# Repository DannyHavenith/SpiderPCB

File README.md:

Hardware Design for the Spider Home Automation Hub
==================================================
These files contain the schema and PCB-design for spider. More details in the 
[spider firmware repository](https://github.com/DannyHavenith/spider).

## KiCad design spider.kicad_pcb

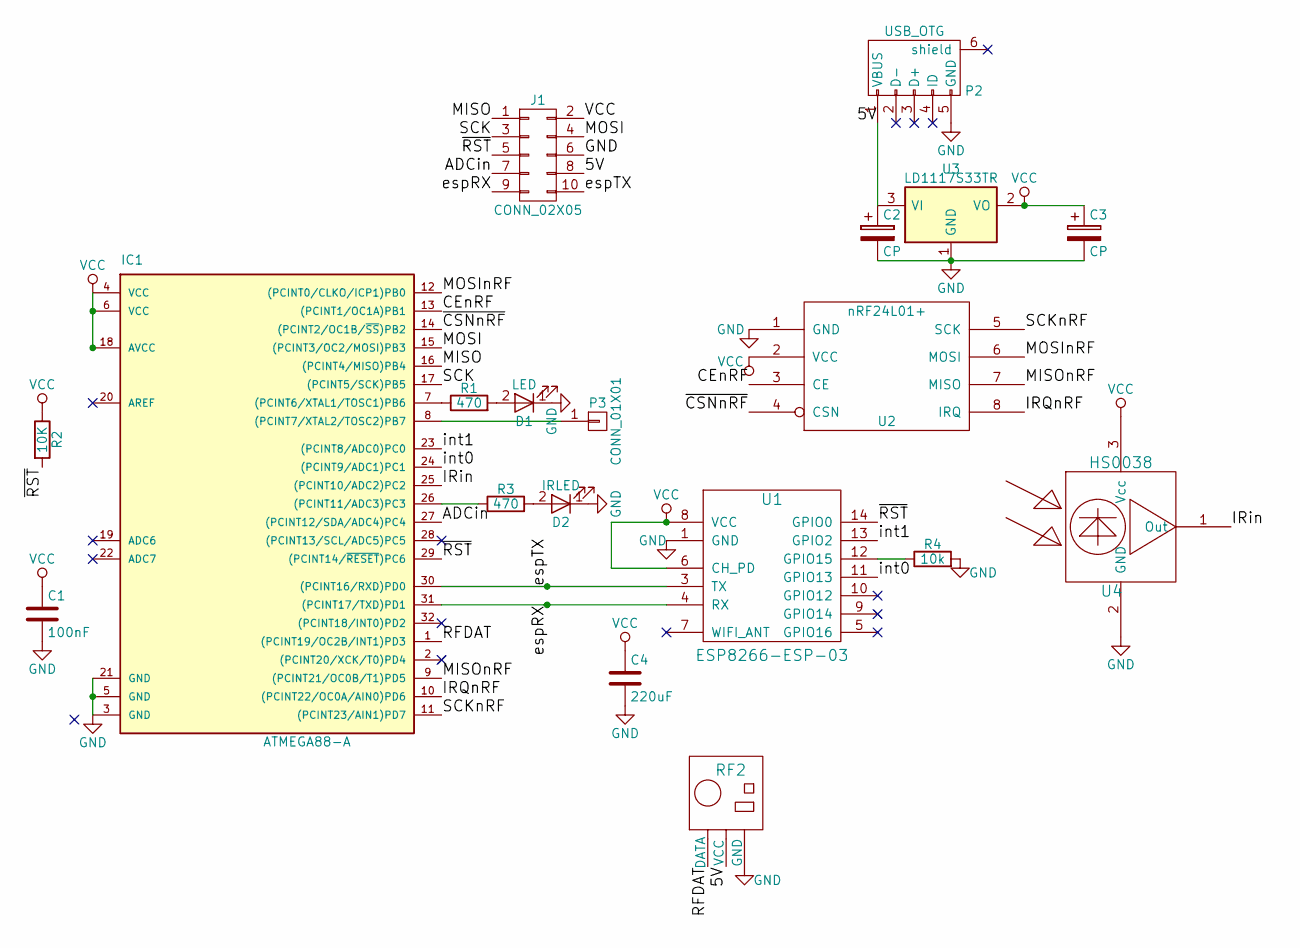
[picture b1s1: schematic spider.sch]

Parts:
C1: 100nF; C_0805
C2, C3: CP; CP_Elec_4x5.3
C4: 220uF; C_0805
D1: LED; LED_0805
D2: IRLED; LED_D5.0mm
IC1: ATMEGA88-A; TQFP-32_7x7mm_Pitch0.8mm
J1: CONN_02X05; Pin_Header_Straight_2x05_Pitch2.54mm
P2: USB_OTG; USB_Micro-B handsoldering
P3: CONN_01X01; Pin_Header_Straight_1x01_Pitch2.00mm
R1, R3: 470; R_0805_HandSoldering
R2: 10K; R_0805_HandSoldering
R4: 10k; R_0805_HandSoldering
RF2: 433 MHz; RF_Transmitter_433_MHz
U1: ESP8266-ESP-03
U2: nRF24L01+; NRF24L01_MODULE
U3: LD1117S33TR; SOT-223-3Lead_TabPin2
U4: HS0038; TSOP2438_long

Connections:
/5V: C2.1, J1.8, P2.1 (VBUS), RF2.2 (VCC), U3.3 (VI)
/ADCin: IC1.27 ((PCINT12/SDA/ADC4)PC4), J1.7
/CEnRF: IC1.13 ((PCINT1/OC1A)PB1), U2.3 (CE)
/IRQnRF: IC1.10 ((PCINT22/OC0A/AIN0)PD6), U2.8 (IRQ)
/IRin: IC1.25 ((PCINT10/ADC2)PC2), U4.1 (Out)
/MISO: IC1.16 ((PCINT4/MISO)PB4), J1.1
/MISOnRF: IC1.9 ((PCINT21/OC0B/T1)PD5), U2.7 (MISO)
/MOSI: IC1.15 ((PCINT3/OC2/MOSI)PB3), J1.4
/MOSInRF: IC1.12 ((PCINT0/CLKO/ICP1)PB0), U2.6 (MOSI)
/RFDAT: IC1.1 ((PCINT19/OC2B/INT1)PD3), RF2.1 (DATA)
/SCK: IC1.17 ((PCINT5/SCK)PB5), J1.3
/SCKnRF: IC1.11 ((PCINT23/AIN1)PD7), U2.5 (SCK)
/espRX: IC1.31 ((PCINT17/TXD)PD1), J1.9, U1.4 (RX)
/espTX: IC1.30 ((PCINT16/RXD)PD0), J1.10, U1.3 (TX)
/int0: IC1.24 ((PCINT9/ADC1)PC1), U1.11 (GPIO13)
/int1: IC1.23 ((PCINT8/ADC0)PC0), U1.13 (GPIO2)
/~CSNnRF: IC1.14 ((PCINT2/OC1B/~SS~)PB2), U2.4 (CSN)
/~RST: IC1.29 ((PCINT14/~RESET~)PC6), J1.5, R2.2, U1.14 (GPIO0)
GND: C1.2, C2.2, C3.2, C4.2, D1.1 (K), D2.1 (K), IC1.3 (GND), IC1.5 (GND), IC1.21 (GND), J1.6, P2.5 (GND), R4.2, RF2.3 (GND), U1.1 (GND), U2.1 (GND), U3.1 (GND), U4.2 (GND)
unnamed: D1.2 (A), R1.2
unnamed: D2.2 (A), R3.2
unnamed: IC1.7 ((PCINT6/XTAL1/TOSC1)PB6), R1.1
unnamed: IC1.8 ((PCINT7/XTAL2/TOSC2)PB7), P3.1
unnamed: IC1.26 ((PCINT11/ADC3)PC3), R3.1
unnamed: R4.1, U1.12 (GPIO15)
VCC: C1.1, C3.1, C4.1, IC1.4 (VCC), IC1.6 (VCC), IC1.18 (AVCC), J1.2, R2.1, U1.6 (CH_PD), U1.8 (VCC), U2.2 (VCC), U3.2 (VO), U4.3 (Vcc)

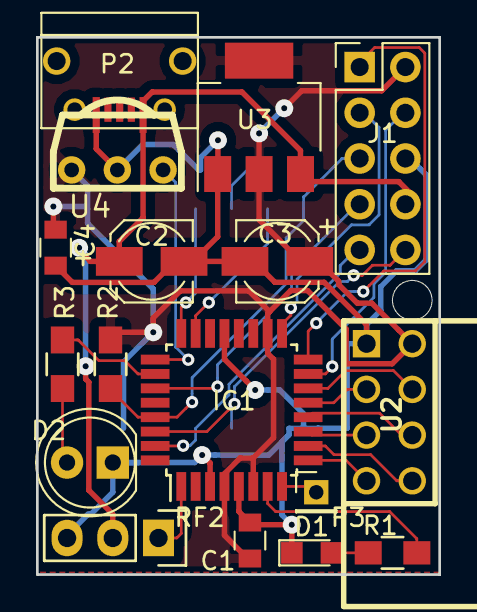
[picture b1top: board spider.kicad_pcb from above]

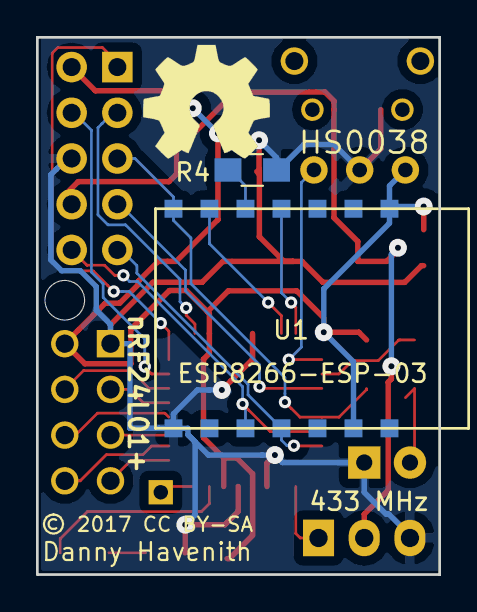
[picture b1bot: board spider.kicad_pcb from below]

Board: 2 copper layers, 22.4 x 29.8 mm, 20 parts (3 on the bottom side), 26 nets.

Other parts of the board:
© 2017 CC BY-SA: Danny Havenith; oshardware

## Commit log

2017-03-30 Add everything that was created in a long time period
2017-06-11 Add more expansion pins, route 5V to transmitter, add small fixes.
2017-06-11 Clean up component files.
